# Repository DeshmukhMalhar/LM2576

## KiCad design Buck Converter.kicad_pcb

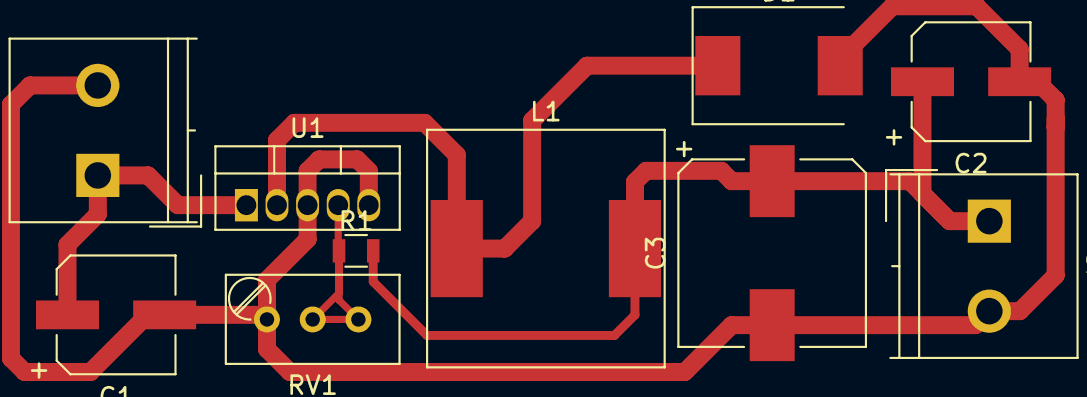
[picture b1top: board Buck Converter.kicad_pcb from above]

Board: 2 copper layers, 10 parts (0 on the bottom side), 5 nets.

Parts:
C1, C2: CP; CP_Elec_6.3x5.8
C3: CP; CP_Elec_10x10.5
D1: D_Schottky; D_SMC
J1, J2: Screw_Terminal_01x02; TerminalBlock_Philmore_TB132_02x5mm_Straight
L1: L_Core_Ferrite; L_Neosid_SM-NE127
R1: R; R_0805
RV1: POT; Potentiometer_Trimmer_Bourns_3296W
U1: LM2576S-ADJ; TO-220-5_Vertical

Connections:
/VOUT: C2.1, C3.1, J2.1, L1.2, R1.2
GND: C1.2, C2.2, C3.2, D1.2, J1.2, J2.2, RV1.1, U1.3, U1.5
unnamed: D1.1, L1.1, U1.2
unnamed: R1.1, RV1.2, RV1.3, U1.4
VCC: C1.1, J1.1, U1.1

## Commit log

2018-09-20 Through hole design
2018-10-04 Start of modifications for Through Hole version
2019-10-05 change cap footprint
